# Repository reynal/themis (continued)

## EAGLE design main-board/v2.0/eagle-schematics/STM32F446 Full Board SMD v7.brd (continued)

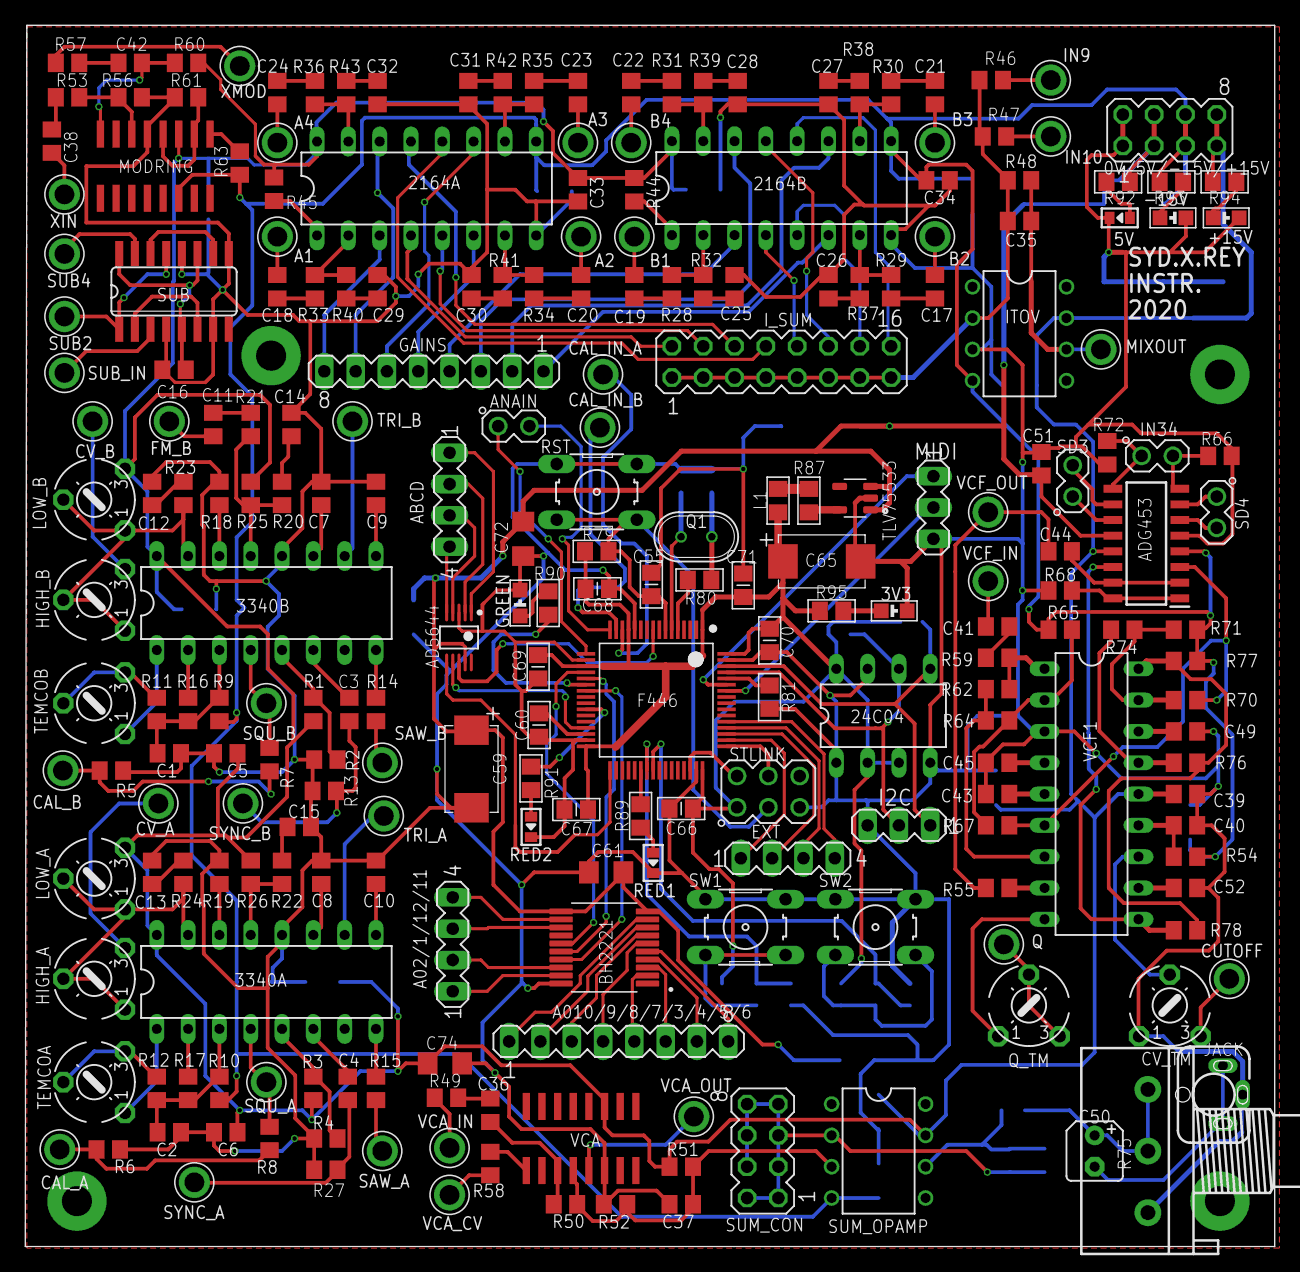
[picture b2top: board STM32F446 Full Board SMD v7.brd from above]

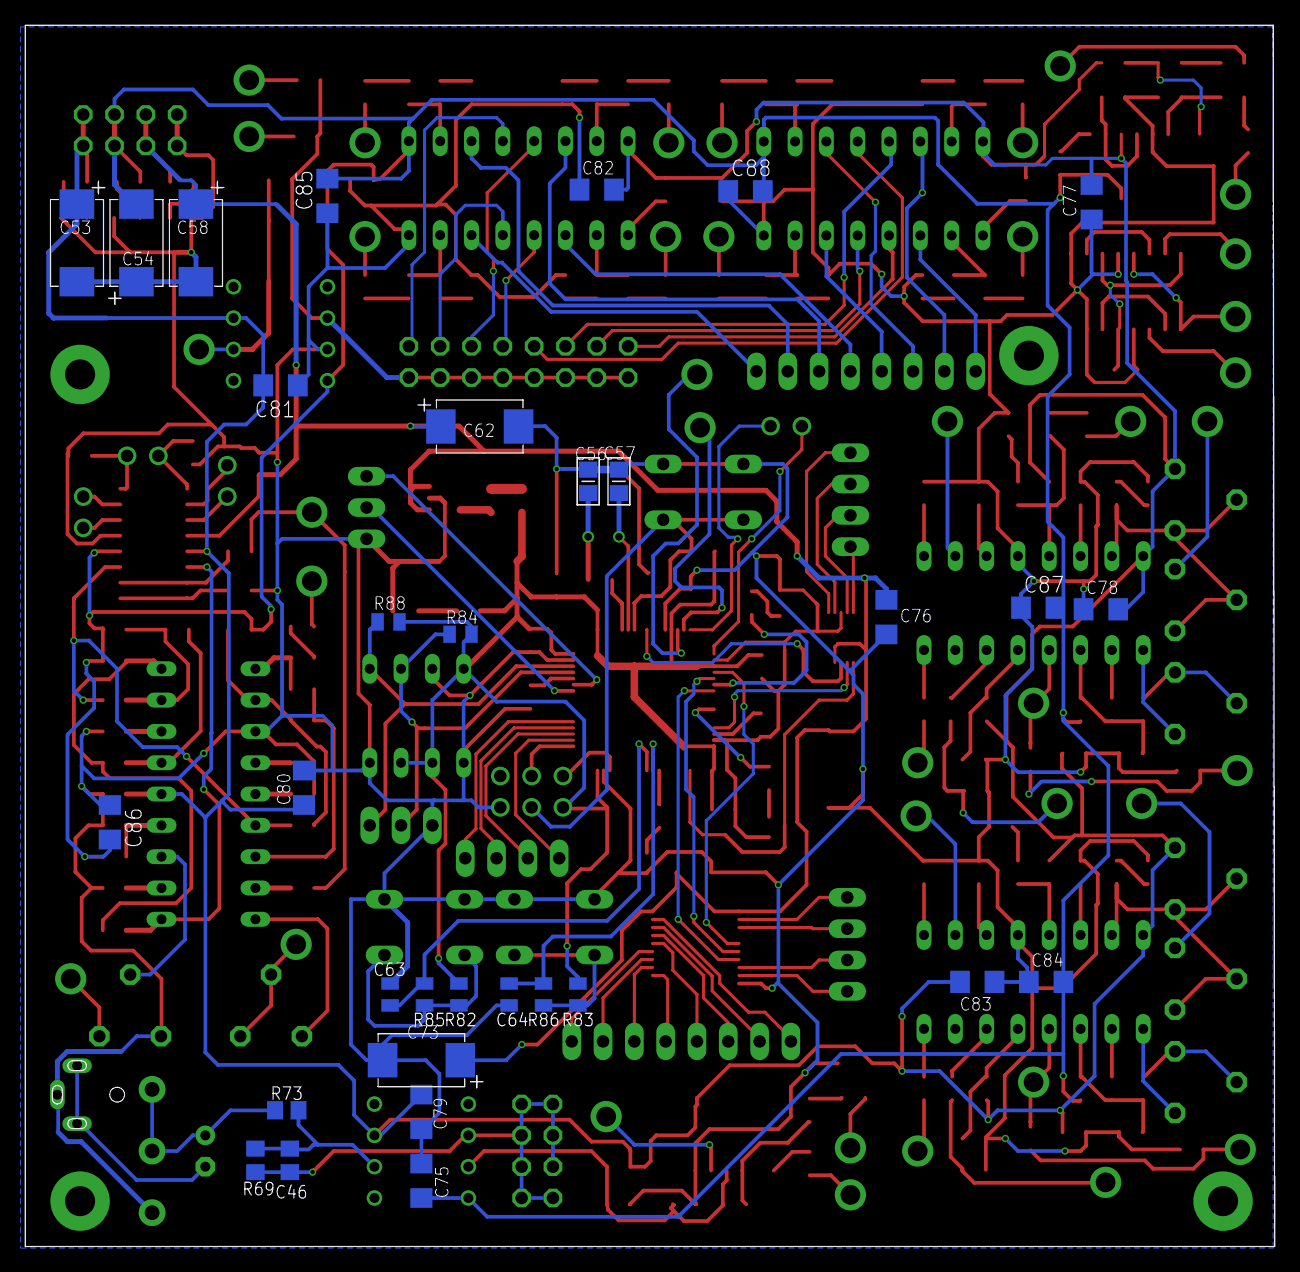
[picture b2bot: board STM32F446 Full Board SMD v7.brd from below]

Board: 2 copper layers, 101.3 x 99.1 mm, 275 parts (32 on the bottom side), 213 nets.

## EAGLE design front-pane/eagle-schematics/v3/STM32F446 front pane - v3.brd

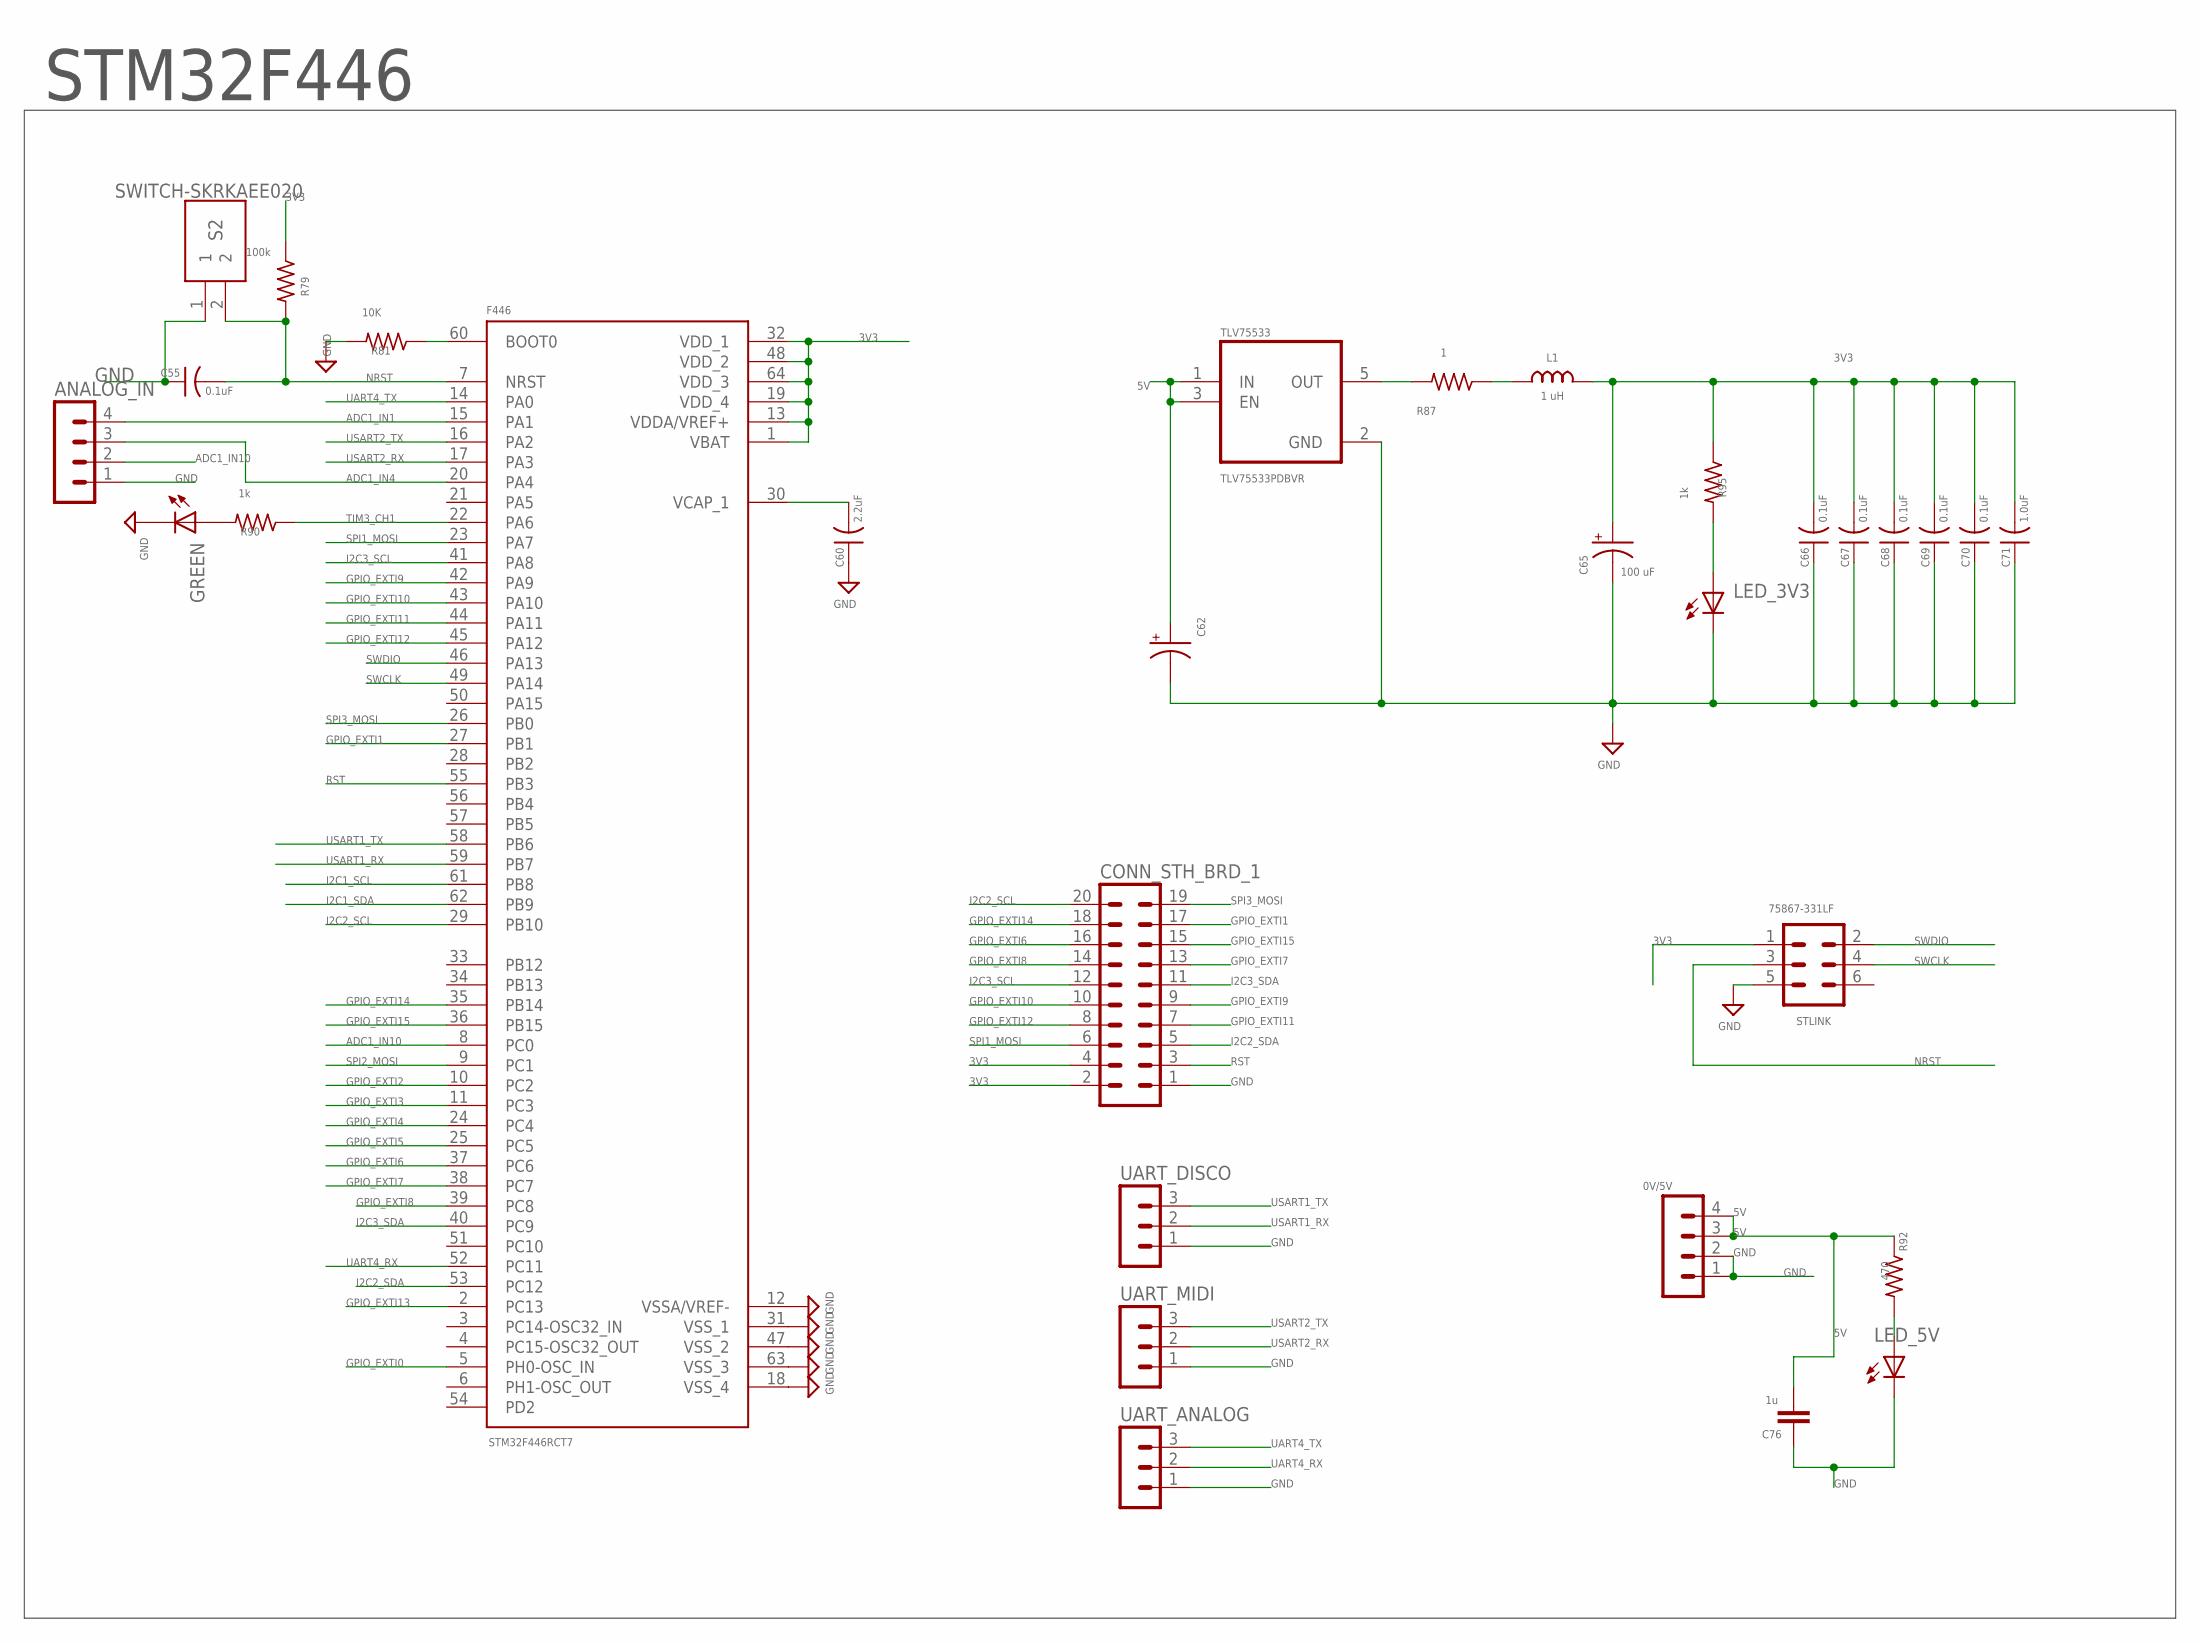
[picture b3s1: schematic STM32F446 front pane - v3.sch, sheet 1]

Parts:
0V/5V: PINHEADER-M04PL; MA04-1
ANALOG_IN: MA04-1
C55, C66, C67, C68, C69, C70: 0.1uF; C0805
C60: 2.2uF; C0805
C62: 10u; CPOL2917
C65: 100 uF; CPOL2917
C71: 1.0uF; C0805
C76: 1u; C1206
CONN_STH_BRD_1: MA10-2
F446: STM32F446RCT7; QFP50P1200X1200X160-64N
GREEN: LED-0805; 0805-LED
L1: 1 uH; L0805
LED_3V3: LED-0805; 0805-LED
LED_5V: LED-0603; 0603-LED
R79: 100k; R0805
R81: 10K; R0805
R87: 1; R0805
R90, R95: 1k; R0805
R92: 470; R0805
S2: SWITCH-SKRKAEE020; SKRKAEE020
STLINK: 75867-331LF; MA03-2
TLV75533: TLV75533PDBVR; SOT95P280X145-5N
UART_ANALOG: MA03-1
UART_DISCO: MA03-1
UART_MIDI: MA03-1

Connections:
3V3: C65.+, C66.2, C67.2, C68.2, C69.2, C70.2, C71.2, CONN_STH_BRD_1.2, CONN_STH_BRD_1.4, F446.1 (VBAT), F446.13 (VDDA/VREF+), F446.19 (VDD_4), F446.32 (VDD_1), F446.48 (VDD_2), F446.64 (VDD_3), L1.2, R79.1, R95.1, STLINK.1; also elsewhere on the board
5V: 0V/5V.3, 0V/5V.4, C62.+, C76.2, R92.1, TLV75533.1 (IN), TLV75533.3 (EN)
ADC1_IN1: ANALOG_IN.4, F446.15 (PA1)
ADC1_IN4: ANALOG_IN.3, F446.20 (PA4)
ADC1_IN10: ANALOG_IN.2, F446.8 (PC0)
BOOT1: F446.60 (BOOT0), R81.1
GND: 0V/5V.1, 0V/5V.2, ANALOG_IN.1, C55.1, C60.1, C62.-, C65.-, C66.1, C67.1, C68.1, C69.1, C70.1, C71.1, C76.1, CONN_STH_BRD_1.1, F446.12 (VSSA/VREF-), F446.18 (VSS_4), F446.31 (VSS_1), F446.47 (VSS_2), F446.63 (VSS_3), GREEN.C, LED_3V3.C, LED_5V.C, R81.2, S2.1, STLINK.5, TLV75533.2 (GND), UART_ANALOG.1, UART_DISCO.1, UART_MIDI.1; also elsewhere on the board
GPIO_EXTI0: F446.5 (PH0-OSC_IN); also elsewhere on the board
GPIO_EXTI1: CONN_STH_BRD_1.17, F446.27 (PB1)
GPIO_EXTI2: F446.10 (PC2); also elsewhere on the board
GPIO_EXTI3: F446.11 (PC3); also elsewhere on the board
GPIO_EXTI4: F446.24 (PC4); also elsewhere on the board
GPIO_EXTI5: F446.25 (PC5); also elsewhere on the board
GPIO_EXTI6: CONN_STH_BRD_1.16, F446.37 (PC6)
GPIO_EXTI7: CONN_STH_BRD_1.13, F446.38 (PC7)
GPIO_EXTI8: CONN_STH_BRD_1.14, F446.39 (PC8)
GPIO_EXTI9: CONN_STH_BRD_1.9, F446.42 (PA9)
GPIO_EXTI10: CONN_STH_BRD_1.10, F446.43 (PA10)
GPIO_EXTI11: CONN_STH_BRD_1.7, F446.44 (PA11)
GPIO_EXTI12: CONN_STH_BRD_1.8, F446.45 (PA12)
GPIO_EXTI13: F446.2 (PC13); also elsewhere on the board
GPIO_EXTI14: CONN_STH_BRD_1.18, F446.35 (PB14)
GPIO_EXTI15: CONN_STH_BRD_1.15, F446.36 (PB15)
I2C1_SCL: F446.61 (PB8); also elsewhere on the board
I2C1_SDA: F446.62 (PB9); also elsewhere on the board
I2C2_SCL: CONN_STH_BRD_1.20, F446.29 (PB10); also elsewhere on the board
I2C2_SDA: CONN_STH_BRD_1.5, F446.53 (PC12); also elsewhere on the board
I2C3_SCL: CONN_STH_BRD_1.12, F446.41 (PA8); also elsewhere on the board
I2C3_SDA: CONN_STH_BRD_1.11, F446.40 (PC9); also elsewhere on the board
unnamed: LED_5V.A, R92.2
unnamed: GREEN.A, R90.2
unnamed: LED_3V3.A, R95.2
unnamed: R87.2, TLV75533.5 (OUT)
unnamed: L1.1, R87.1
NRST: C55.2, F446.7 (NRST), R79.2, S2.2, STLINK.3
RST: CONN_STH_BRD_1.3, F446.55 (PB3); also elsewhere on the board
SPI1_MOSI: CONN_STH_BRD_1.6, F446.23 (PA7); also elsewhere on the board
SPI2_MOSI: F446.9 (PC1); also elsewhere on the board
SPI3_MOSI: CONN_STH_BRD_1.19, F446.26 (PB0); also elsewhere on the board
SWCLK: F446.49 (PA14), STLINK.4
SWDIO: F446.46 (PA13), STLINK.2
TIM3_CH1: F446.22 (PA6), R90.1
UART4_RX: F446.52 (PC11), UART_ANALOG.2
UART4_TX: F446.14 (PA0), UART_ANALOG.3
USART1_RX: F446.59 (PB7), UART_DISCO.2
USART1_TX: F446.58 (PB6), UART_DISCO.3
USART2_RX: F446.17 (PA3), UART_MIDI.2
USART2_TX: F446.16 (PA2), UART_MIDI.3
VCAP1: C60.2, F446.30 (VCAP_1)

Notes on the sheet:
STM32F446

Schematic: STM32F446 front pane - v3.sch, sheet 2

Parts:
C4, C5, C6, C7, C8, C9, C10, C11, C12, C16, C17, C18, C22, C23, C24, C28, C29, C30, C34, C35, C36, C40, C41, C42, C46, C47, C48: 10n; 0805-CAP
CB1, CB2, CB4, CB6: 10n; 0805-CAP
CDEC_1, CDEC_2, CDEC_3, CDEC_4, CDEC_5, CDEC_6, CDEC_7, CDEC_8, CDEC_9, CDEC_10, CDEC_11, CDEC_12, CDEC_13: 100n; 1206
CDEC_11A, CDEC_12A: 10u; CPOL2917
CDEC_11B, CDEC_12B: 100n; 0805-CAP
CONN_STH_BRD_2: MA10-2
ENC_11, ENC_13, ENC_14, ENC_21, ENC_23: ENCODER-RGB-SWITCH-NO_NUT; ENCODER_LED_3
LED1, LED2, LED6, LED22: CZXR-80RGB03-A; LED4-2.0-D8.0MM
MCP_000, MCP_001: MCP23017; SOIC-28
PIXEL_11, PIXEL_12, PIXEL_13, PIXEL_14, PIXEL_21, PIXEL_22, PIXEL_23, PIXEL_24, PIXEL_31, PIXEL_32, PIXEL_33, PIXEL_34, PIXEL_35: NEOPIXEL-TLC59731DR; SOIC127P600X175-8N
R3, R6, R7, R8, R9, R10, R11, R12, R17, R18, R19, R24, R25, R26, R31, R35, R36, R37, R38, R39, R40, R48, R49, R50, R52, R53, R54, R66, R67, R68, R82, R84, R85, R102, R103, R104, R116, R117, R118: 100; 1206
R4, R5, R186, R187: 1k; R0805
R13, R20, R27, R41, R55, R69, R88, R105, R119: 10k; 1206
R14, R15, R16, R21, R22, R23, R28, R29, R30, R42, R43, R44, R56, R57, R58, R70, R71, R72, R89, R91, R93, R106, R107, R108, R120, R121, R122: 470; 1206
RB1, RB2, RB4, RB6: 470; 1206
S24, S31, S34, S35: ENCODER-RGB-SWITCH-NO_NUT; ENCODER_LED_3
S32, S33: B3F-1000
S_12, S_22: B3F-1000

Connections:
3V3: CDEC_1.1, CDEC_2.1, CDEC_3.1, CDEC_4.1, CDEC_5.1, CDEC_6.1, CDEC_7.1, CDEC_8.1, CDEC_9.1, CDEC_10.1, CDEC_11.1, CDEC_11A.+, CDEC_11B.1, CDEC_12.1, CDEC_12A.+, CDEC_12B.1, CDEC_13.1, CONN_STH_BRD_2.2, CONN_STH_BRD_2.4, ENC_11.5 (+), ENC_13.5 (+), ENC_14.5 (+), ENC_21.5 (+), ENC_23.5 (+), LED1.2 (+), LED2.2 (+), LED6.2 (+), LED22.2 (+), MCP_000.9 (VDD), MCP_001.9 (VDD), MCP_001.15 (A0), PIXEL_11.8 (VCC), PIXEL_12.8 (VCC), PIXEL_13.8 (VCC), PIXEL_14.8 (VCC), PIXEL_21.8 (VCC), PIXEL_22.8 (VCC), PIXEL_23.8 (VCC), PIXEL_24.8 (VCC), PIXEL_31.8 (VCC), PIXEL_32.8 (VCC), PIXEL_33.8 (VCC), PIXEL_34.8 (VCC), PIXEL_35.8 (VCC), R4.2, R5.2, R186.2, R187.2, S24.5 (+), S31.5 (+), S34.5 (+), S35.5 (+); also elsewhere on the board
DATA_PIXEL11: PIXEL_11.5 (SDO), PIXEL_21.6 (SDI)
DATA_PIXEL12: PIXEL_11.6 (SDI), PIXEL_12.5 (SDO)
DATA_PIXEL13: PIXEL_12.6 (SDI), PIXEL_13.5 (SDO)
DATA_PIXEL14: PIXEL_13.6 (SDI), PIXEL_14.5 (SDO)
DATA_PIXEL21: PIXEL_21.5 (SDO), PIXEL_22.6 (SDI)
DATA_PIXEL22: PIXEL_22.5 (SDO), PIXEL_23.6 (SDI)
DATA_PIXEL23: PIXEL_23.5 (SDO), PIXEL_24.6 (SDI)
DATA_PIXEL24: PIXEL_24.5 (SDO), PIXEL_35.6 (SDI)
DATA_PIXEL32: PIXEL_31.6 (SDI), PIXEL_32.5 (SDO)
DATA_PIXEL33: PIXEL_32.6 (SDI), PIXEL_33.5 (SDO)
DATA_PIXEL34: PIXEL_33.6 (SDI), PIXEL_34.5 (SDO)
DATA_PIXEL35: PIXEL_34.6 (SDI), PIXEL_35.5 (SDO)
GND: C4.1, C5.1, C6.2, C7.1, C8.1, C9.2, C10.1, C11.1, C12.2, C16.1, C17.1, C18.2, C22.1, C23.1, C24.2, C28.1, C29.1, C30.2, C34.1, C35.1, C36.2, C40.1, C41.1, C42.2, C46.1, C47.1, C48.2, CB1.1, CB2.1, CB4.1, CB6.1, CDEC_1.2, CDEC_2.2, CDEC_3.2, CDEC_4.2, CDEC_5.2, CDEC_6.2, CDEC_7.2, CDEC_8.2, CDEC_9.2, CDEC_10.2, CDEC_11.2, CDEC_11A.-, CDEC_11B.2, CDEC_12.2, CDEC_12A.-, CDEC_12B.2, CDEC_13.2, CONN_STH_BRD_2.1, ENC_11.C, ENC_13.C, ENC_14.C, ENC_21.C, ENC_23.C, MCP_000.10 (VSS), MCP_000.15 (A0), MCP_000.16 (A1), MCP_000.17 (A2), MCP_001.10 (VSS), MCP_001.16 (A1), MCP_001.17 (A2), PIXEL_11.4 (GND), PIXEL_12.4 (GND), PIXEL_13.4 (GND), PIXEL_14.4 (GND), PIXEL_21.4 (GND), PIXEL_22.4 (GND), PIXEL_23.4 (GND), PIXEL_24.4 (GND), PIXEL_31.4 (GND), PIXEL_32.4 (GND), PIXEL_33.4 (GND), PIXEL_34.4 (GND), PIXEL_35.4 (GND), R13.2, R20.2, R27.2, R41.2, R55.2, R69.2, R88.2, R105.2, R119.2, S24.C, S31.C, S32.1, S32.2, S33.1, S33.2, S34.C, S35.C, S_12.1, S_12.2, S_22.1, S_22.2; also elsewhere on the board
GPA0_11: MCP_000.21 (GPA0), R71.1, S24.B
GPA0_12: MCP_001.21 (GPA0), R121.1, S35.B
GPA1_11: MCP_000.22 (GPA1), R70.1, S24.A
GPA1_12: MCP_001.22 (GPA1), R119.1, R122.1, S35.3 (SW)
GPA2_11: MCP_000.23 (GPA2), R69.1, R72.1, S24.3 (SW)
GPA2_12: MCP_001.23 (GPA2), R120.1, S35.A
GPA3_11: ENC_23.A, MCP_000.24 (GPA3), R56.1
GPA3_12: MCP_001.24 (GPA3), R107.1, S34.B
GPA4_11: ENC_23.B, MCP_000.25 (GPA4), R57.1
GPA4_12: MCP_001.25 (GPA4), R106.1, S34.A
GPA5_11: ENC_23.3 (SW), MCP_000.26 (GPA5), R55.1, R58.1
GPA5_12: MCP_001.26 (GPA5), R105.1, R108.1, S34.3 (SW)
GPA6_11: ENC_11.3 (SW), MCP_000.27 (GPA6), R13.1, R16.1
GPA6_12: MCP_001.27 (GPA6), RB6.1, S33.3, S33.4
GPA7_11: MCP_000.28 (GPA7), RB2.1, S_12.3, S_12.4
GPA7_12: MCP_001.28 (GPA7), RB1.1, S32.3, S32.4
GPB0_11: ENC_11.A, MCP_000.1 (GPB0), R14.1
GPB1_11: ENC_11.B, MCP_000.2 (GPB1), R15.1
GPB1_12: MCP_001.2 (GPB1), R91.1, S31.B
GPB2_11: ENC_13.A, MCP_000.3 (GPB2), R21.1
GPB2_12: MCP_001.3 (GPB2), R88.1, R93.1, S31.3 (SW)
GPB3_11: ENC_13.B, MCP_000.4 (GPB3), R22.1
GPB3_12: MCP_001.4 (GPB3), R89.1, S31.A
GPB4_11: ENC_13.3 (SW), MCP_000.5 (GPB4), R20.1, R23.1
GPB4_12: ENC_21.3 (SW), MCP_001.5 (GPB4), R41.1, R44.1
GPB5_11: ENC_14.3 (SW), MCP_000.6 (GPB5), R27.1, R30.1
GPB5_12: ENC_21.A, MCP_001.6 (GPB5), R42.1
GPB6_11: ENC_14.A, MCP_000.7 (GPB6), R28.1
GPB6_12: ENC_21.B, MCP_001.7 (GPB6), R43.1
GPB7_11: ENC_14.B, MCP_000.8 (GPB7), R29.1
GPB7_12: MCP_001.8 (GPB7), RB4.1, S_22.3, S_22.4
I2C2_SCL: CONN_STH_BRD_2.20; also elsewhere on the board
I2C2_SDA: CONN_STH_BRD_2.5; also elsewhere on the board
I2C3_SCL: CONN_STH_BRD_2.12, MCP_000.12 (SCL), MCP_001.12 (SCL), R4.1, R186.1; also elsewhere on the board
I2C3_SDA: CONN_STH_BRD_2.11, MCP_000.13 (SDA), MCP_001.13 (SDA), R5.1, R187.1; also elsewhere on the board
INTA_2: CONN_STH_BRD_2.13; also elsewhere on the board
INTA_11: CONN_STH_BRD_2.8, MCP_000.20 (INTA)
INTA_12: CONN_STH_BRD_2.9, MCP_001.20 (INTA)
INTA_31: CONN_STH_BRD_2.18; also elsewhere on the board
INTA_32: CONN_STH_BRD_2.15; also elsewhere on the board
INTB_2: CONN_STH_BRD_2.14; also elsewhere on the board
INTB_11: CONN_STH_BRD_2.7, MCP_000.19 (INTB)
INTB_12: CONN_STH_BRD_2.10, MCP_001.19 (INTB)
INTB_31: CONN_STH_BRD_2.17; also elsewhere on the board
INTB_32: CONN_STH_BRD_2.16; also elsewhere on the board
unnamed: PIXEL_32.1 (OUT0), R3.1
unnamed: PIXEL_32.2 (OUT1), R6.1
unnamed: ENC_11.1 (-R), R10.2
unnamed: ENC_11.2 (-G), R11.2
unnamed: ENC_11.4 (-B), R12.2
unnamed: PIXEL_11.1 (OUT0), R10.1
unnamed: PIXEL_11.2 (OUT1), R11.1
unnamed: PIXEL_11.3 (OUT2), R12.1
unnamed: C4.2, R14.2
unnamed: C5.2, R15.2
unnamed: C6.1, R16.2
unnamed: ENC_13.1 (-R), R17.2
unnamed: ENC_13.2 (-G), R18.2
unnamed: ENC_13.4 (-B), R19.2
unnamed: PIXEL_13.1 (OUT0), R17.1
unnamed: PIXEL_13.2 (OUT1), R18.1
unnamed: PIXEL_13.3 (OUT2), R19.1
unnamed: C7.2, R21.2
unnamed: C8.2, R22.2
unnamed: C9.1, R23.2
unnamed: ENC_14.1 (-R), R24.2
unnamed: ENC_14.2 (-G), R25.2
unnamed: ENC_14.4 (-B), R26.2
unnamed: PIXEL_14.1 (OUT0), R24.1
unnamed: PIXEL_14.2 (OUT1), R25.1
unnamed: PIXEL_14.3 (OUT2), R26.1
unnamed: C10.2, R28.2
unnamed: C11.2, R29.2
unnamed: C12.1, R30.2
unnamed: PIXEL_32.3 (OUT2), R7.1
unnamed: CB1.2, RB1.2
unnamed: LED1.1 (R), R7.2
unnamed: LED1.4 (B), R6.2
unnamed: LED1.3 (G), R3.2
unnamed: PIXEL_12.1 (OUT0), R8.1
unnamed: PIXEL_12.2 (OUT1), R9.1
unnamed: PIXEL_12.3 (OUT2), R31.1
unnamed: CB2.2, RB2.2
unnamed: ENC_21.1 (-R), R38.2
unnamed: ENC_21.2 (-G), R39.2
unnamed: ENC_21.4 (-B), R40.2
unnamed: PIXEL_21.1 (OUT0), R38.1
unnamed: PIXEL_21.2 (OUT1), R39.1
unnamed: PIXEL_21.3 (OUT2), R40.1
unnamed: C16.2, R42.2
unnamed: C17.2, R43.2
unnamed: C18.1, R44.2
unnamed: LED2.1 (R), R31.2
unnamed: LED2.4 (B), R9.2
unnamed: LED2.3 (G), R8.2
unnamed: ENC_23.1 (-R), R52.2
unnamed: ENC_23.2 (-G), R53.2
unnamed: ENC_23.4 (-B), R54.2
unnamed: PIXEL_23.1 (OUT0), R52.1
unnamed: PIXEL_23.2 (OUT1), R53.1
unnamed: PIXEL_23.3 (OUT2), R54.1
unnamed: C22.2, R56.2
unnamed: C23.2, R57.2
unnamed: C24.1, R58.2
unnamed: PIXEL_22.1 (OUT0), R35.1
unnamed: PIXEL_22.2 (OUT1), R36.1
unnamed: PIXEL_22.3 (OUT2), R37.1
unnamed: CB4.2, RB4.2
unnamed: LED22.1 (R), R37.2
unnamed: LED22.4 (B), R36.2
unnamed: LED22.3 (G), R35.2
unnamed: R66.2, S24.1 (-R)
unnamed: R67.2, S24.2 (-G)
unnamed: R68.2, S24.4 (-B)
unnamed: PIXEL_24.1 (OUT0), R66.1
unnamed: PIXEL_24.2 (OUT1), R67.1
unnamed: PIXEL_24.3 (OUT2), R68.1
unnamed: C28.2, R70.2
unnamed: C29.2, R71.2
unnamed: C30.1, R72.2
unnamed: R82.2, S31.1 (-R)
unnamed: R84.2, S31.2 (-G)
unnamed: R85.2, S31.4 (-B)
unnamed: PIXEL_31.1 (OUT0), R82.1
unnamed: PIXEL_31.2 (OUT1), R84.1
unnamed: PIXEL_31.3 (OUT2), R85.1
unnamed: C34.2, R89.2
unnamed: C35.2, R91.2
unnamed: C36.1, R93.2
unnamed: PIXEL_33.1 (OUT0), R48.1
unnamed: PIXEL_33.2 (OUT1), R49.1
unnamed: PIXEL_33.3 (OUT2), R50.1
unnamed: CB6.2, RB6.2
unnamed: LED6.1 (R), R50.2
unnamed: LED6.4 (B), R49.2
unnamed: LED6.3 (G), R48.2
unnamed: R102.2, S34.1 (-R)
unnamed: R103.2, S34.2 (-G)
unnamed: R104.2, S34.4 (-B)
unnamed: PIXEL_34.1 (OUT0), R102.1
unnamed: PIXEL_34.2 (OUT1), R103.1
unnamed: PIXEL_34.3 (OUT2), R104.1
unnamed: C40.2, R106.2
unnamed: C41.2, R107.2
unnamed: C42.1, R108.2
unnamed: R116.2, S35.1 (-R)
unnamed: R117.2, S35.2 (-G)
unnamed: R118.2, S35.4 (-B)
unnamed: PIXEL_35.1 (OUT0), R116.1
unnamed: PIXEL_35.2 (OUT1), R117.1
unnamed: PIXEL_35.3 (OUT2), R118.1
unnamed: C46.2, R120.2
unnamed: C47.2, R121.2
unnamed: C48.1, R122.2
PIXEL42: PIXEL_14.6 (SDI); also elsewhere on the board
RST: CONN_STH_BRD_2.3, MCP_000.18 (!RESET), MCP_001.18 (!RESET); also elsewhere on the board
SPI1_MOSI: CONN_STH_BRD_2.6; also elsewhere on the board
SPI3_MOSI: CONN_STH_BRD_2.19; also elsewhere on the board

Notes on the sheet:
RGB ENCODER 11
RGB ENCODER 13
RGB ENCODER 14
RGB ENCODER 21
RGB ENCODER 23
RGB ENCODER 24
RGB ENCODER 31
RGB ENCODER 34
RGB ENCODER 35
OSCILLATORS
SWITCH RGB 12
SWITCH RGB 22
SWITCH RGB 33
SWITCH RGB 32
MCP 11 & 12
